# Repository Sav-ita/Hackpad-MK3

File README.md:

# Hackpad MK3

This repository contains all files for the **Hackpad MK3** project, a custom 9-key macro pad designed for productivity and customization.

It features:
- 3x3 mechanical keys (9 total)
- 0.91" OLED display (SSD1306)
- Powered by an RP2040 microcontroller (compatible with CircuitPython)

---

## 📸 Hackpad Overview

The Hackpad MK2 is designed with a sleek and compact form factor, perfect for desktop shortcuts and macros.

---

## 🔌 Schematic

The schematic, designed in KiCad, shows the wiring for the 9 independent keys and the I2C OLED display. Each key is connected to a dedicated GPIO on the RP2040, and the OLED follows the GND-VCC-SCL-SDA pinout.

---

## 🖥️ PCB Layout
The PCB was designed focusing on a clean layout and easy assembly. It includes custom silkscreen labeling and broad copper traces for reliability.

---

## 🧩 Case Design

The case consists of two main parts: the base and the top cover, designed to be 3D printed and fit perfectly with the PCB.

---

## 📦 Bill of Materials (BOM)
List of all components used in this project:

| Part | Quantity | Description | 
|------|----------|-------------|
| Mechanical Key Switches | 9 | MX-style switches |
| Keycaps | 9 | Compatible with MX switches | 
| RP2040 Microcontroller | 1 | e.g., Seeed XIAO RP2040 | 
| OLED Display 0.91" | 1 | 128x32 I2C interface | 
| Custom PCB | 1 | Hackpad MK2 Design | 
| 3D Printed Case | 1 | Base + Cover | 

---

## Firmware Instructions

1. Download and install the latest **CircuitPython** .uf2 for your board.
2. Connect the RP2040 via USB and copy the firmware files.
3. Ensure the following libraries are in the `lib` folder:
   - `adafruit_display_text`
   - `adafruit_ssd1306`
   - `adafruit_hid`
4. Copy `main.py` (or rename to `code.py`) to the device.

## 📝 License
This project is open-source and created by **Saverio Martino**.

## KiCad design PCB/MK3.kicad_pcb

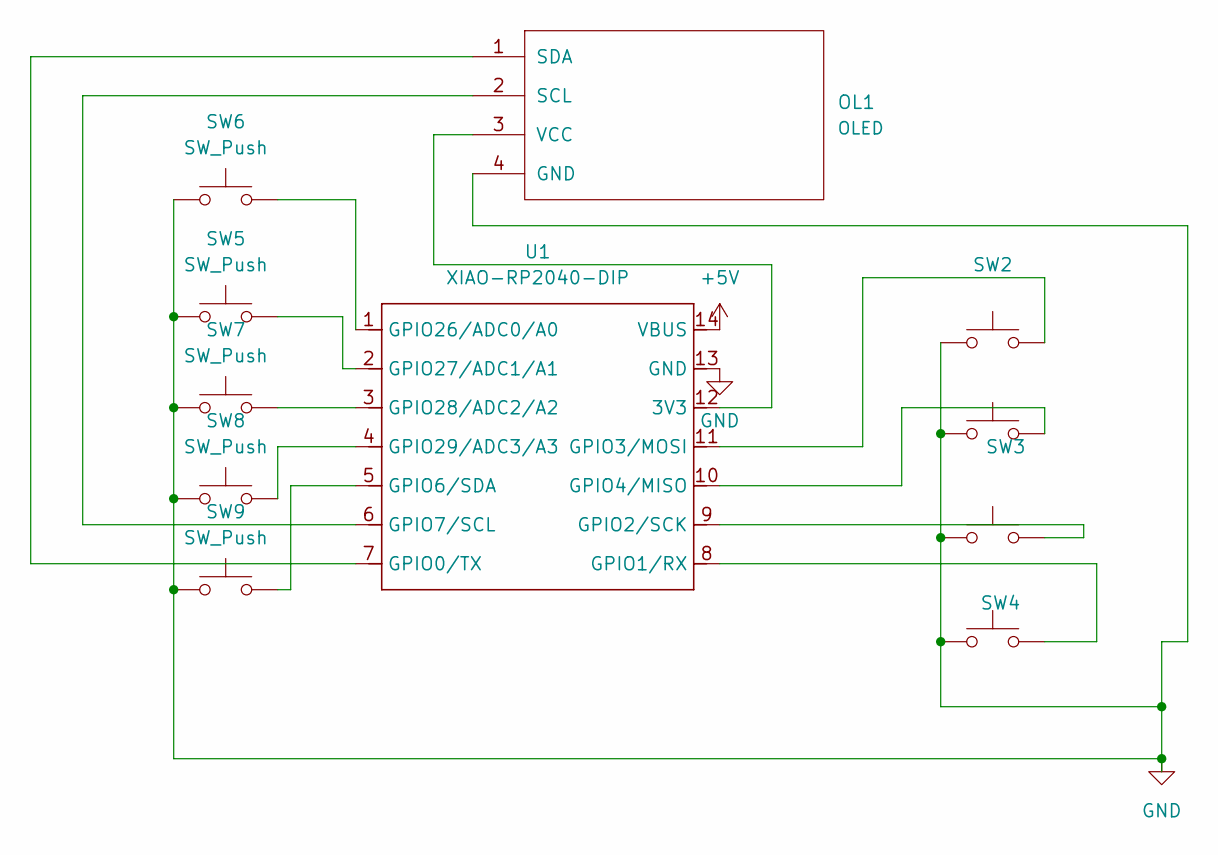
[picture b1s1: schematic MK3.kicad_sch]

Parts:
OL1: OLED
SW1, SW2, SW3, SW4, SW5, SW6, SW7, SW8, SW9: SW_Push; SW_Cherry_MX_1.00u_PCB
U1: XIAO-RP2040-DIP

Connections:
+5V: U1.14 (VBUS)
GND: OL1.4 (GND), SW1.1, SW2.1, SW3.1, SW4.1, SW5.1, SW6.1, SW7.1, SW8.1, SW9.1, U1.13 (GND)
unnamed: OL1.2 (SCL), U1.6 (GPIO7/SCL)
unnamed: OL1.1 (SDA), U1.7 (GPIO0/TX)
unnamed: OL1.3 (VCC), U1.12 (3V3)
unnamed: SW4.2, U1.8 (GPIO1/RX)
unnamed: SW3.2, U1.9 (GPIO2/SCK)
unnamed: SW2.2, U1.11 (GPIO3/MOSI)
unnamed: SW1.2, U1.10 (GPIO4/MISO)
unnamed: SW9.2, U1.5 (GPIO6/SDA)
unnamed: SW6.2, U1.1 (GPIO26/ADC0/A0)
unnamed: SW5.2, U1.2 (GPIO27/ADC1/A1)
unnamed: SW7.2, U1.3 (GPIO28/ADC2/A2)
unnamed: SW8.2, U1.4 (GPIO29/ADC3/A3)

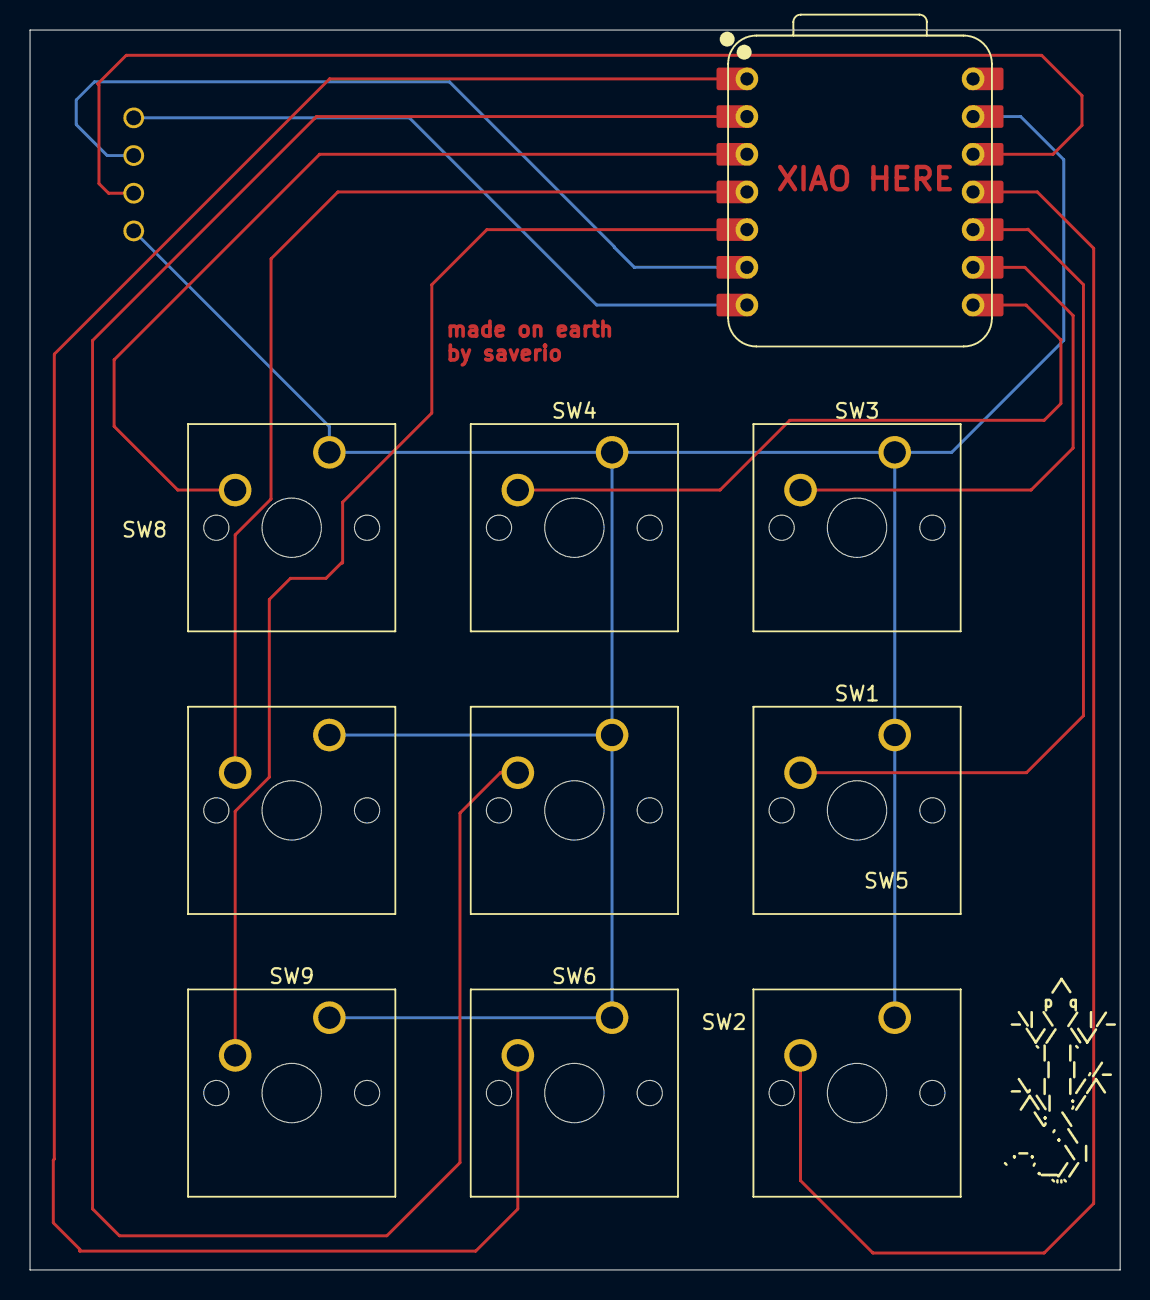
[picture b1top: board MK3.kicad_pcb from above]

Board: 2 copper layers, 73.5 x 83.6 mm, 11 parts (0 on the bottom side), 13 nets.

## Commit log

2026-02-15 update README
    update README
2026-02-17 Add PCB image to README
